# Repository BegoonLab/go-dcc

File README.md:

# NRMA Digital Command Control (DCC) Implementation in Go

This project is a comprehensive kit for controlling model trains using the NMRA Digital Command Control (DCC) protocol. It includes software and hardware design, integration with Raspberry Pi, and a mobile-friendly application for seamless control on mobile devices. In addition, the project offers a solution for controlling train modules, such as servos and lights, in a model train diorama.

The implementation is based on the following NMRA standards:

* [S-9.1 Electrical Standard](https://www.nmra.org/sites/default/files/standards/sandrp/pdf/s-9.1_electrical_standards_for_digital_command_control_2021.pdf)
* [S-9.2 DCC Communications Standard](http://www.nmra.org/sites/default/files/s-92-2004-07.pdf)
* [S-9.2.1 Extended Packet Formats for Digital Command Control Standard](http://www.nmra.org/sites/default/files/s-9.2.1_2012_07.pdf)

## Features

- Full DCC protocol implementation for controlling model trains and DCC Accessories modules
- Hardware design for Raspberry Pi integration
- Mobile-friendly application with zero overhead, compatible with any mobile phone
- Control solution for train modules, including servos and lights in model train dioramas

## Demo
[Mobile client application demo](https://begoonlab.tech/demos/train-commander/demo.index.html) 

## Installation

1. Clone this repository:
```bash
git clone https://github.com/yourusername/yourrepository.git
```

## Usage
Ensure your Raspberry Pi is set up and connected to your model train and DCC Accessories modules.

Run the compiled executable to start the server:

```bash
./yourrepository
```
Open the mobile-friendly application on your phone by navigating to the server's IP address and port number.

Use the application's interface to control your model train and DCC Accessories modules.

## Contributing
We welcome contributions to this project! Please follow these steps:

1. Fork the repository
2. Create a new branch (`git checkout -b your-feature`)
3. Commit your changes (`git commit -m 'Add a new feature`)
4. Push to the branch (`git push origin your-feature`)
5. Create a new Pull Request

## License
This project is licensed under the MIT License.

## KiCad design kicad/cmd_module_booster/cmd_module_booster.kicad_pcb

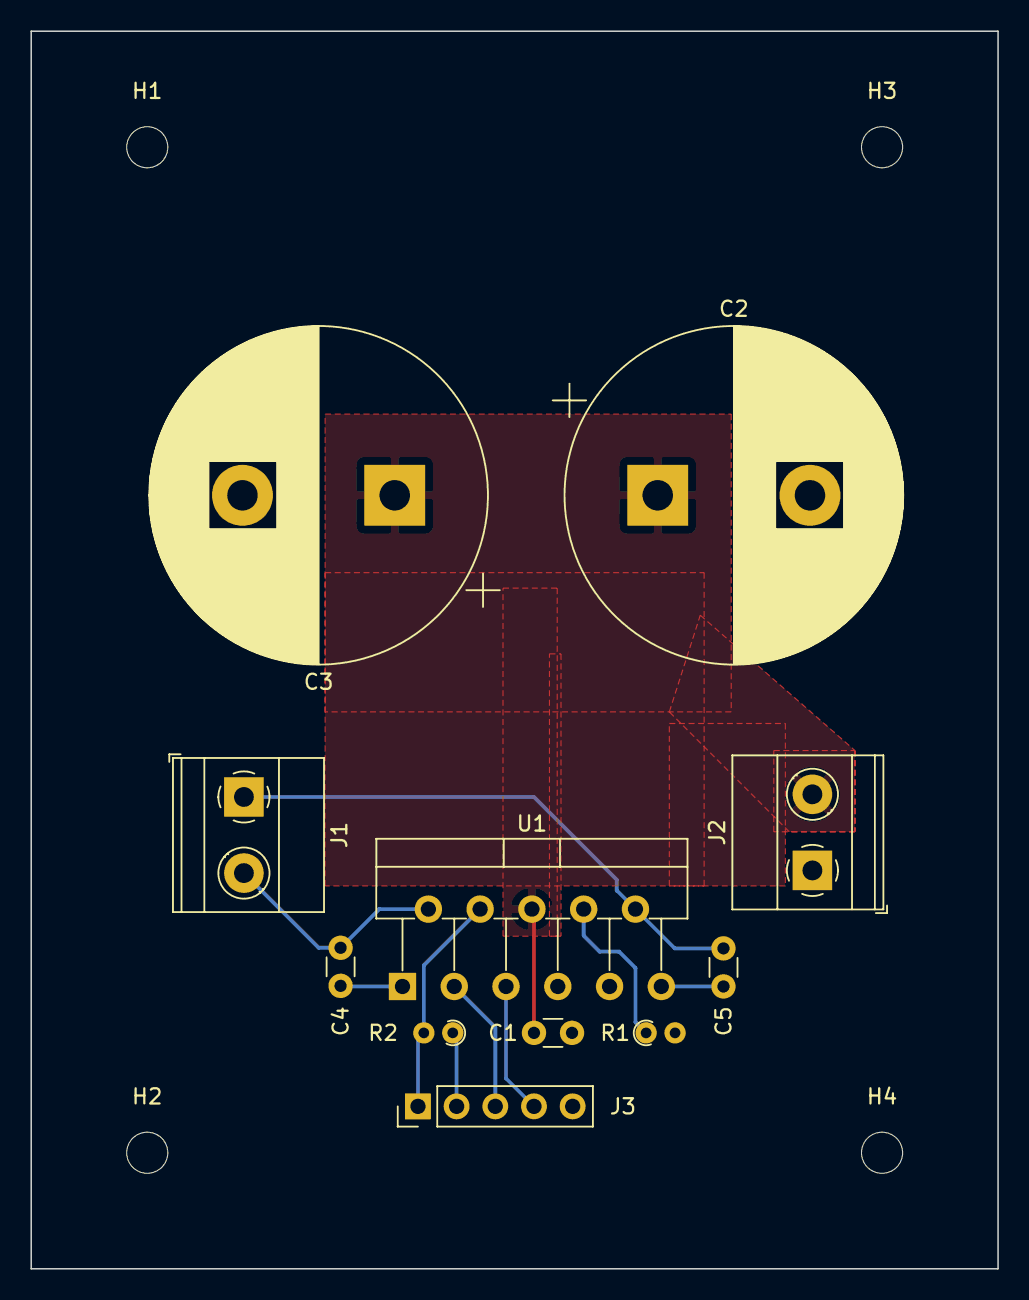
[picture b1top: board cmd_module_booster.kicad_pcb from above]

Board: 2 copper layers, 63.5 x 81.3 mm, 15 parts (0 on the bottom side), 11 nets.

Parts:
C1, C4, C5: 10n; C_Disc_D3.0mm_W1.6mm_P2.50mm
C2, C3: 4.7m; CP_Radial_D22.0mm_P10.00mm_SnapIn
H1, H2, H3, H4: MountingHole; MountingHole_2.7mm_M2.5
J1: Rails; TerminalBlock_Phoenix_MKDS-1,5-2_1x02_P5.00mm_Horizontal
J2: Power; TerminalBlock_Phoenix_MKDS-1,5-2_1x02_P5.00mm_Horizontal
J3: RPi Connect; PinHeader_1x05_P2.54mm_Vertical
R1: 3.3k; R_Axial_DIN0204_L3.6mm_D1.6mm_P1.90mm_Vertical
R2: 10k; R_Axial_DIN0204_L3.6mm_D1.6mm_P1.90mm_Vertical
U1: LMD18200; TO-220-11_P3.4x5.08mm_StaggerOdd_Lead4.85mm_Vertical

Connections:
3V3_RPi: J3.2, R2.1
5V_RPi: J3.4, U1.5
+18V: C1.1, C2.1, C3.1, J2.2, U1.6
GND: C1.2, C2.2, C3.2, J2.1, J3.5, R1.2, U1.7
GPIO17_RPi: J3.3, U1.3
GPIO27_RPi: J3.1, R2.2, U1.4
unnamed: C4.2, U1.1
unnamed: C5.1, U1.11
unnamed: R1.1, U1.8
Rails0: C4.1, J1.2, U1.2
Rails1: C5.2, J1.1, U1.10

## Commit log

2021-11-01 Add KiCAD project to repo
2021-11-01 Change power supply capacitor
2021-11-01 Added 1 version of gerber
2021-11-01 Add step model of command booster
2021-11-06 Add cmd module box 3D model
2021-11-23 Creating UI for Cmd module
2021-11-24 Creating UI
2021-11-28 Create UI
2021-12-14 Fix reboot / poweroff
2021-12-14 Add autostart
2021-12-18 Add connection notification Work on speed control Add etalon oscillograms
2021-12-19 Fix speed control to be 28 steps compatible
2021-12-19 Add thumb label to speed slider
2022-01-02 Add Function Group Two Instruction
2022-01-02 Add Function Expansion Instruction
2023-02-11 upgrade deps
2023-02-11 Refactor a project
2023-02-13 Add firmware for a Railway module
2023-02-13 Upgrade docs
2023-02-18 Add railway module CAD files v1.0
2023-02-19 Upgrade vue.js Upgrade js assets
2023-02-19 Add support of binary (protobuf) communication over websockets Upgrade UI
2023-02-22 Upgrade UI Upgrade Server
2023-03-04 Upgrade railway module firmware
2023-03-04 Upgrade UI
2023-03-24 Fix buttons padding Upgrade node deps
2023-03-24 Fix reset button bug
2023-12-10 Add build flags Improve docs
2023-12-10 Add build flags
2023-12-10 Adjust config
2023-12-10 Fix UI issues with accordion
